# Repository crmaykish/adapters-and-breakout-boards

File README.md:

# Adapters and Breakout Boards

Here's a collection of various adapter PCBs I've made. Hopefully you find some of them useful. All design is done in KiCAD and Gerbers are provided.

## DIP Adapters

Adapters that convert surface-mount footprints to DIP

[1. PLCC-32 to DIP-32](PLCC-32-to-DIP-32/)

[2. SOJ-36 to DIP-32 SRAM](SOJ-36-to-DIP-32-SRAM/)

Converts 512KB SRAM chips from SOJ to DIP. Note: the address and data pins are scrambled to facilitate routing, but this is transparent to the connecting devices.

## Specialty Adapters

Specific and/or odd use case adapters

[1. MC68SEC000-to-DIP-64](MC68SEC000-to-DIP-64/)

Breaks out a 64 pin 68SEC000 CPU into a DIP-64 footprint mostly compatible with the full size 68000/68010. If the two jumpers are closed, this will run in 8 bit mode and connect the A0 line to where the E pin would normally be on a full size 68000. Leave the jumpers open to use this as a drop-in replacement.

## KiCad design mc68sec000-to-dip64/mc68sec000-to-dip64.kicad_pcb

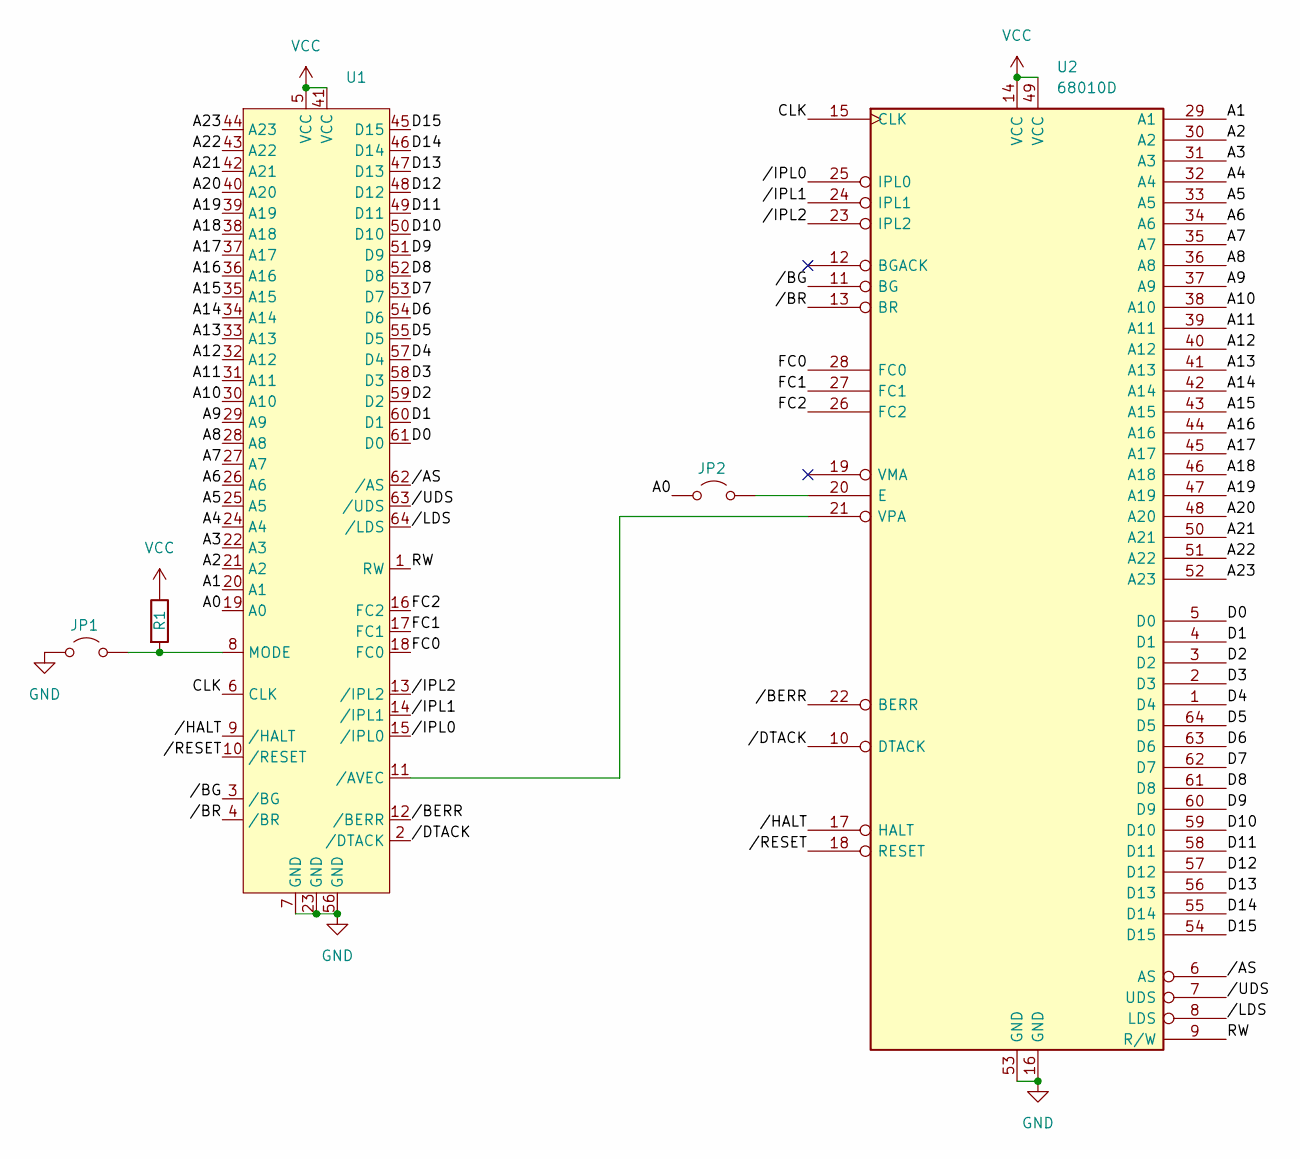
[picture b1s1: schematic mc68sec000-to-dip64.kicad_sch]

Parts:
JP1, JP2: Jumper_2_Open; PinHeader_1x02_P2.54mm_Vertical
R1: R; R_1206_3216Metric_Pad1.30x1.75mm_HandSolder
U1: LQFP-64_14x14mm_P0.8mm
U2: 68010D; DIP-64_W22.86mm

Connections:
/A0: JP2.1 (A), U1.19 (A0)
/A1: U1.20 (A1), U2.29 (A1)
/A2: U1.21 (A2), U2.30 (A2)
/A3: U1.22 (A3), U2.31 (A3)
/A4: U1.24 (A4), U2.32 (A4)
/A5: U1.25 (A5), U2.33 (A5)
/A6: U1.26 (A6), U2.34 (A6)
/A7: U1.27 (A7), U2.35 (A7)
/A8: U1.28 (A8), U2.36 (A8)
/A9: U1.29 (A9), U2.37 (A9)
/A10: U1.30 (A10), U2.38 (A10)
/A11: U1.31 (A11), U2.39 (A11)
/A12: U1.32 (A12), U2.40 (A12)
/A13: U1.33 (A13), U2.41 (A13)
/A14: U1.34 (A14), U2.42 (A14)
/A15: U1.35 (A15), U2.43 (A15)
/A16: U1.36 (A16), U2.44 (A16)
/A17: U1.37 (A17), U2.45 (A17)
/A18: U1.38 (A18), U2.46 (A18)
/A19: U1.39 (A19), U2.47 (A19)
/A20: U1.40 (A20), U2.48 (A20)
/A21: U1.42 (A21), U2.50 (A21)
/A22: U1.43 (A22), U2.51 (A22)
/A23: U1.44 (A23), U2.52 (A23)
/CLK: U1.6 (CLK), U2.15 (CLK)
/D0: U1.61 (D0), U2.5 (D0)
/D1: U1.60 (D1), U2.4 (D1)
/D2: U1.59 (D2), U2.3 (D2)
/D3: U1.58 (D3), U2.2 (D3)
/D4: U1.57 (D4), U2.1 (D4)
/D5: U1.55 (D5), U2.64 (D5)
/D6: U1.54 (D6), U2.63 (D6)
/D7: U1.53 (D7), U2.62 (D7)
/D8: U1.52 (D8), U2.61 (D8)
/D9: U1.51 (D9), U2.60 (D9)
/D10: U1.50 (D10), U2.59 (D10)
/D11: U1.49 (D11), U2.58 (D11)
/D12: U1.48 (D12), U2.57 (D12)
/D13: U1.47 (D13), U2.56 (D13)
/D14: U1.46 (D14), U2.55 (D14)
/D15: U1.45 (D15), U2.54 (D15)
/FC0: U1.18 (FC0), U2.28 (FC0)
/FC1: U1.17 (FC1), U2.27 (FC1)
/FC2: U1.16 (FC2), U2.26 (FC2)
/RW: U1.1 (RW), U2.9 (R/W)
//AS: U1.62 (/AS), U2.6 (AS)
//BERR: U1.12 (/BERR), U2.22 (BERR)
//BG: U1.3 (/BG), U2.11 (BG)
//BR: U1.4 (/BR), U2.13 (BR)
//DTACK: U1.2 (/DTACK), U2.10 (DTACK)
//HALT: U1.9 (/HALT), U2.17 (HALT)
//IPL0: U1.15 (/IPL0), U2.25 (IPL0)
//IPL1: U1.14 (/IPL1), U2.24 (IPL1)
//IPL2: U1.13 (/IPL2), U2.23 (IPL2)
//LDS: U1.64 (/LDS), U2.8 (LDS)
//RESET: U1.10 (/RESET), U2.18 (RESET)
//UDS: U1.63 (/UDS), U2.7 (UDS)
GND: JP1.1 (A), U1.7 (GND), U1.23 (GND), U1.56 (GND), U2.16 (GND), U2.53 (GND)
unnamed: JP1.2 (B), R1.2, U1.8 (MODE)
unnamed: JP2.2 (B), U2.20 (E)
unnamed: U1.11 (/AVEC), U2.21 (VPA)
VCC: R1.1, U1.5 (VCC), U1.41 (VCC), U2.14 (VCC), U2.49 (VCC)

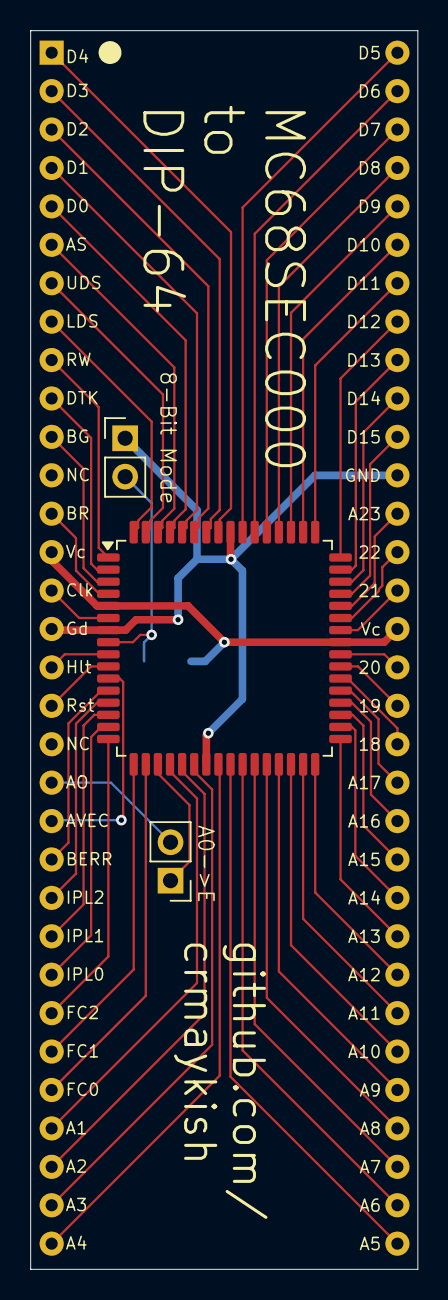
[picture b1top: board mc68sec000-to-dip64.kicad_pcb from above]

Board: 2 copper layers, 25.6 x 81.9 mm, 5 parts (1 on the bottom side), 62 nets.

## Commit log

2024-07-24 Add PLCC-32-to-DIP-32 adapter
2024-07-24 picture of plcc-32-to-dip-32
2024-07-27 Added gerbers for two adapter PCBs
2024-07-31 Add MC68SEC000 to DIP-64 adapter
2024-08-01 Add gerber for MC68SEC000 to DIP adapter
2024-08-01 Add README
2024-08-18 Use larger footprint for MC68SEC000 QFP-64 IC
